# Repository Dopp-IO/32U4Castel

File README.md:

# 32U4Castel
Tiny castellated 32U4 module

Part	Value	      Package  
C1	  0.1uF		    0603-CAP  
C2	  22pF		    0603-CAP  
C3	  0.1uF		    0603-CAP  
C4	  22pF		    0603-CAP  
C5	  1uF		      0603-CAP  
C6	  1uF		      0603-CAP  
C7	  1uF		      0603-CAP  
C8	  1uF		      0603-CAP  
C9	  1uF		      0603-CAP  
C10	  1uF		      0603-CAP  
LED1	Red		      LED-0603  
R1	  10K		      0603-RES  
R2	  22		      0603-RES  
R3	  22		      0603-RES  
R4	  1K		      0603-RES  
U1	  ATMEGA32U4	QFN-44  
Y1	  16MHz		    CRYSTAL-SMD-5X3

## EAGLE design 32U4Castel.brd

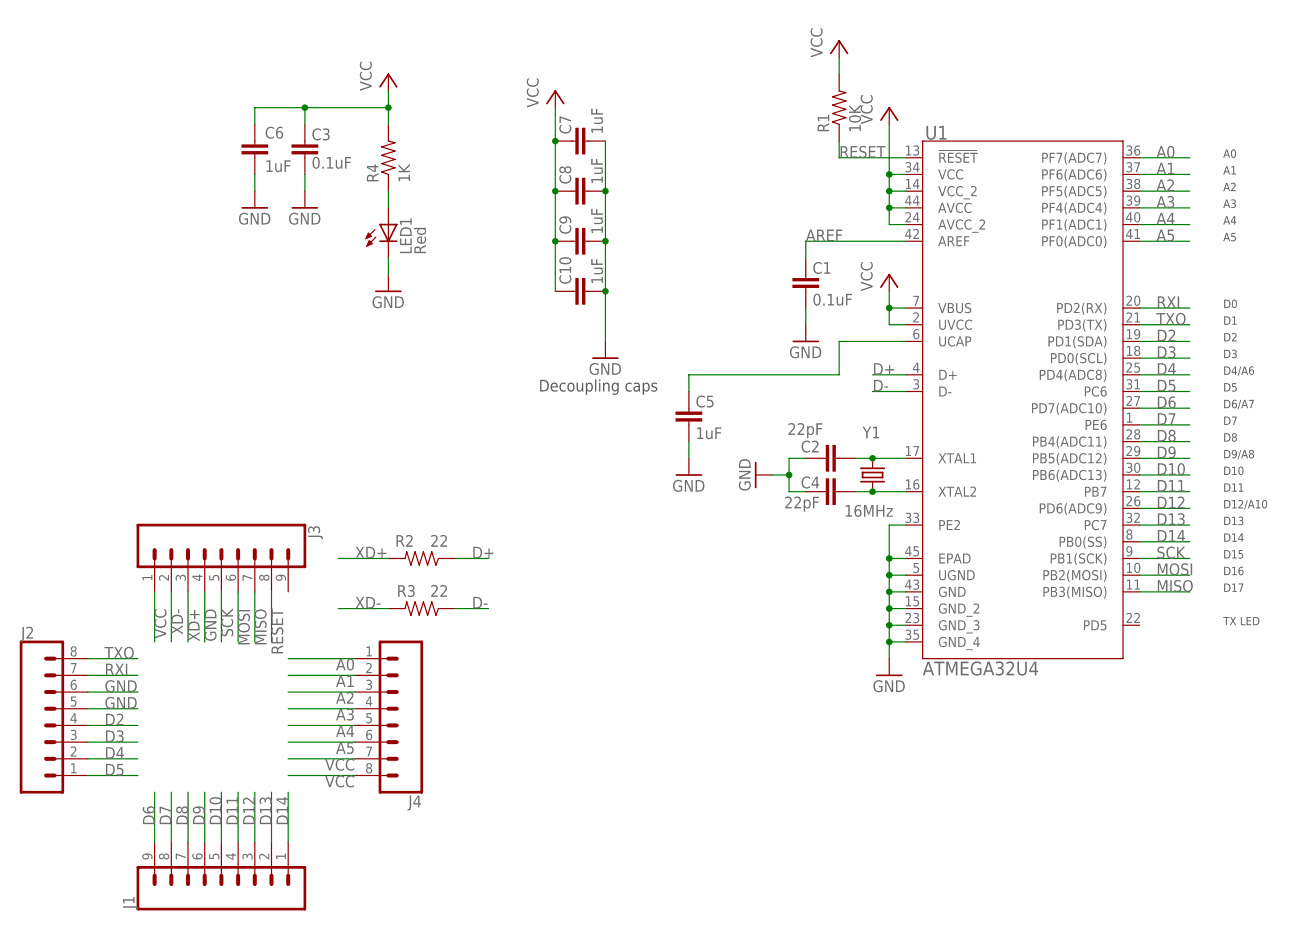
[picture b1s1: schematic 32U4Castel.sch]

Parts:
C1, C3: 0.1uF; 0603-CAP
C2, C4: 22pF; 0603-CAP
C5, C6, C7, C8, C9, C10: 1uF; 0603-CAP
J1, J3: CONN_09NO_SILK; 1X09_NO_SILK
J2, J4: CONN_08NO_SILK_FEMALE_PTH; 1X08_NO_SILK
LED1: Red; LED-0603
R1: 10K; 0603-RES
R2, R3: 22; 0603-RES
R4: 1K; 0603-RES
U1: ATMEGA32U4-MU; 44PW
Y1: 16MHz; CRYSTAL-SMD-5X3

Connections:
A0: J4.1, U1.36 (PF7(ADC7))
A1: J4.2, U1.37 (PF6(ADC6))
A2: J4.3, U1.38 (PF5(ADC5))
A3: J4.4, U1.39 (PF4(ADC4))
A4: J4.5, U1.40 (PF1(ADC1))
A5: J4.6, U1.41 (PF0(ADC0))
AREF: C1.2, U1.42 (AREF)
D2: J2.4, U1.19 (PD1(SDA))
D3: J2.3, U1.18 (PD0(SCL))
D4: J2.2, U1.25 (PD4(ADC8))
D5: J2.1, U1.31 (PC6)
D6: J1.9, U1.27 (PD7(ADC10))
D7: J1.8, U1.1 (PE6)
D8: J1.7, U1.28 (PB4(ADC11))
D9: J1.6, U1.29 (PB5(ADC12))
D10: J1.5, U1.30 (PB6(ADC13))
D11: J1.4, U1.12 (PB7)
D12: J1.3, U1.26 (PD6(ADC9))
D13: J1.2, U1.32 (PC7)
D14: J1.1, U1.8 (PB0(SS))
D+: R2.1, U1.4 (D+)
D-: R3.1, U1.3 (D-)
GND: C1.1, C2.2, C3.1, C4.2, C5.1, C6.2, C7.1, C8.1, C9.1, C10.1, J2.5, J2.6, J3.4, LED1.C, U1.5 (UGND), U1.15 (GND_2), U1.23 (GND_3), U1.33 (PE2), U1.35 (GND_4), U1.43 (GND), U1.45 (EPAD)
LED: LED1.A, R4.1
MISO: J3.7, U1.11 (PB3(MISO))
MOSI: J3.6, U1.10 (PB2(MOSI))
RESET: J3.8, R1.1, U1.13 (!RESET)
RXI: J2.7, U1.20 (PD2(RX))
SCK: J3.5, U1.9 (PB1(SCK))
TXO: J2.8, U1.21 (PD3(TX))
UCAP: C5.2, U1.6 (UCAP)
VCC: C3.2, C6.1, C7.2, C8.2, C9.2, C10.2, J3.1, J4.7, J4.8, R1.2, R4.2, U1.2 (UVCC), U1.7 (VBUS), U1.14 (VCC_2), U1.24 (AVCC_2), U1.34 (VCC), U1.44 (AVCC)
X1: C2.1, U1.17 (XTAL1), Y1.3 (2)
X2: C4.1, U1.16 (XTAL2), Y1.1
XD+: J3.3, R2.2
XD-: J3.2, R3.2

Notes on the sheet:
Decoupling caps

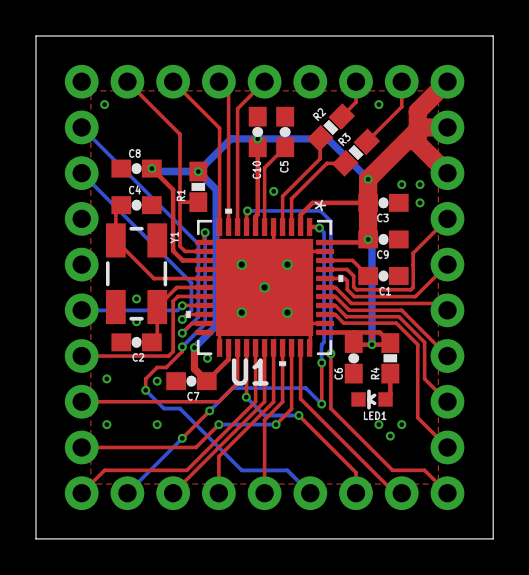
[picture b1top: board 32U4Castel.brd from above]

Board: 2 copper layers, 25.4 x 27.9 mm, 21 parts (0 on the bottom side), 36 nets.

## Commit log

2018-08-10 Added eagle and gerber files
2018-08-10 Added BOM
2018-08-11 Added schematic PDF
2018-08-15 Added pad, complete re-route
    Fabrication was difficult because of non-ground vias where 32U4 wanted a pad. Added pad, rerouted everything. Improved silkscreen.
2018-12-24 Updated 32U4Castel
    Fixed mis-mapped SS pin and improved grounding.
2018-12-24 Updated 32U4
2018-12-24 Added extra decoupling caps

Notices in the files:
parts and their libraries:
SparkFun-Connectors: Licensing: Creative Commons ShareAlike 4.0 International - https://creativecommons.org/licenses/by-sa/4.0
